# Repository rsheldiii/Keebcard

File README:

#Keebcard code

This project is a little rough right now, I had a backup failure that wiped out some of the code. I'll be fixing this up in the coming weeks and getting everything working again.

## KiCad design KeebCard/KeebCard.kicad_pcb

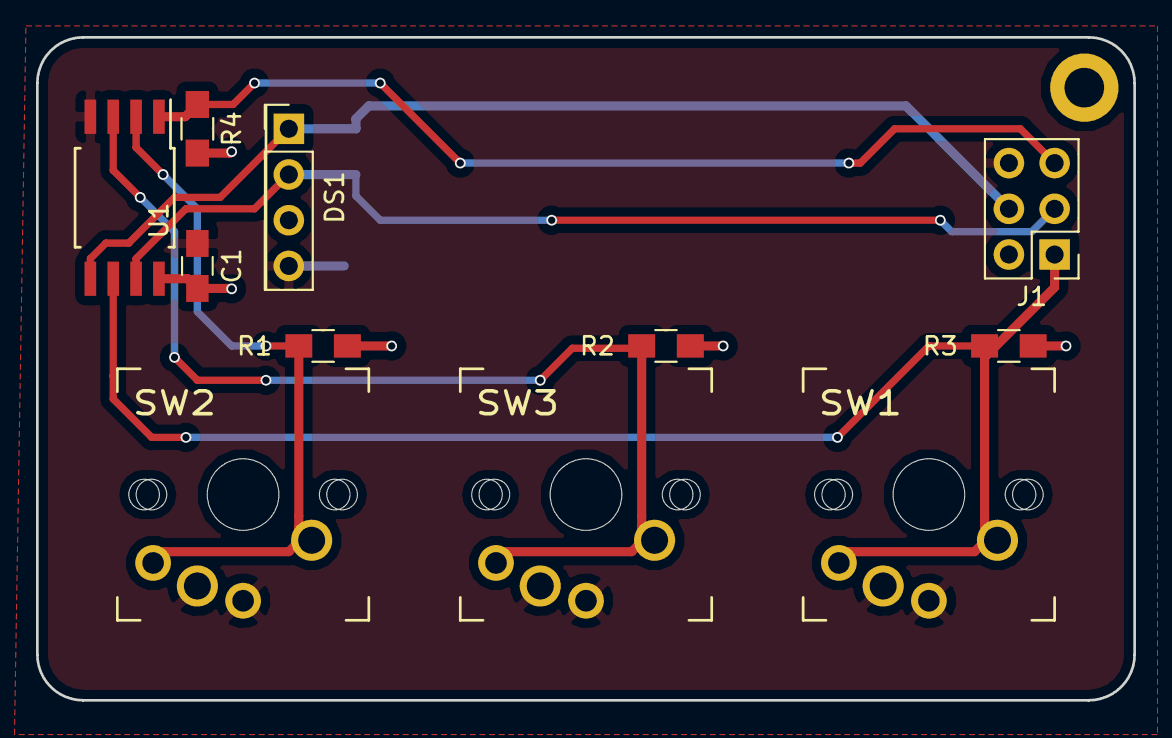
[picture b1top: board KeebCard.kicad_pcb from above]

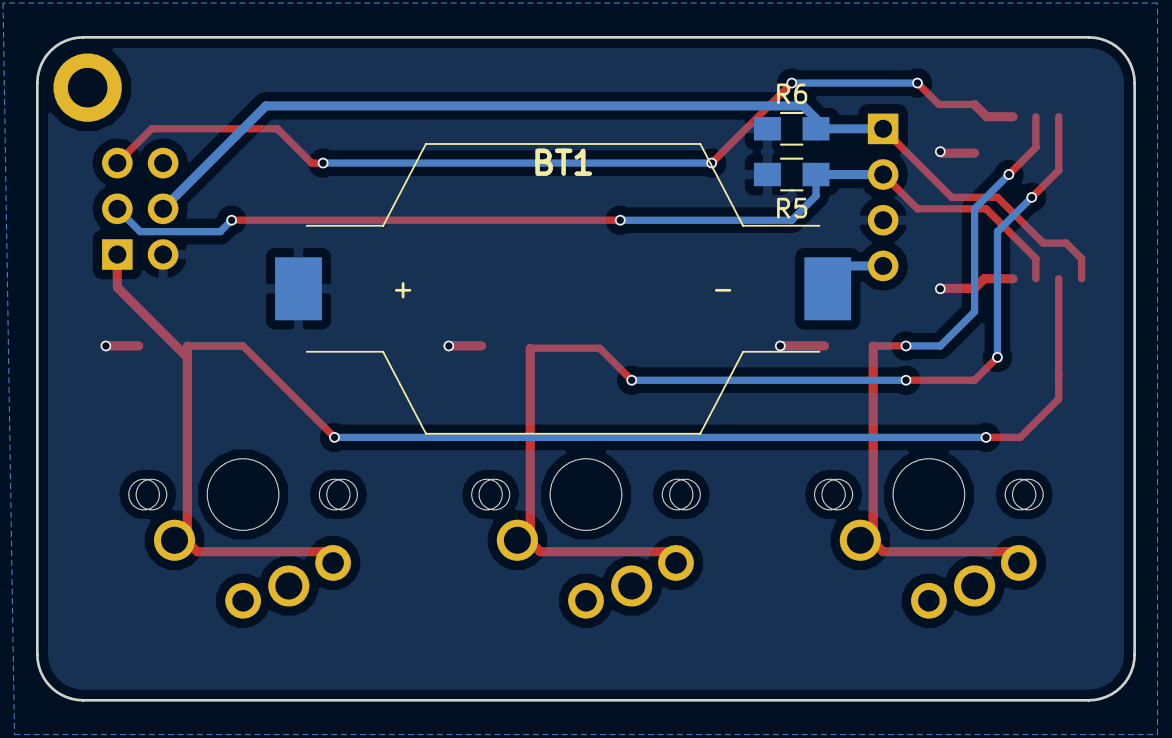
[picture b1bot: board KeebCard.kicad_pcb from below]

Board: 2 copper layers, 61.0 x 36.8 mm, 14 parts (3 on the bottom side), 8 nets.

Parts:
BT1: CR2032; SMTU2032
C1: 100nF; C_0805_HandSoldering
DS1: SSD1306-128x32; SSD1306_OLED_Display_128x32
J1: Conn_02x03_Odd_Even; Pin_Header_Straight_2x03_Pitch2.54mm
R1, R2, R3, R4: 22K; R_0805_HandSoldering
R5, R6: 4.7k; R_0805_HandSoldering
SW1, SW2, SW3: SW_Push; CHERRY_CHOC_PCB
U1: ATTINY85-20SU

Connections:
/PB0: DS1.4, J1.4, R6.1, U1.5
/PB1: J1.1, R3.2, SW1.2, U1.6
/PB2: DS1.3, J1.3, R5.1, U1.7
/PB3: R1.2, SW2.2, U1.2
/PB4: R2.2, SW3.2, U1.3
/PB5: J1.5, R4.1, U1.1
GND: BT1.2, C1.2, DS1.1, J1.6, SW1.1, SW2.1, SW3.1, U1.4
VCC: BT1.1, C1.1, DS1.2, J1.2, R1.1, R2.1, R3.1, R4.2, R5.2, R6.2, U1.8

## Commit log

2019-08-02 Add current code as-is
2019-08-02 Rename README to README.md
2019-08-03 Rename so arduino doesn't complain
2019-08-03 Make compiler happy again
    previously upgraded to a newer version of tiny4koled that doesn't like tiny4koled.h to be included, else there are multiple declaration problems. switched to a pointer and tiny4koled_common.h and it 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
2019-08-09 work on snake a whole bunch
2019-08-10 do even more work on Snake
    I have better commit messages in my professional life I swear
2019-08-19 Update gitignore for Kicad files
2019-08-19 Get Tetris functioning
    not perfect yet
2019-08-19 Add Kicad project
2019-08-19 Add Gerbers
2019-10-02 Last minute PCB changes
2019-10-02 Pong, final version, first pass
2019-10-02 _oled
2019-10-02 revert weird changes
    some weird state accidentally got committed. Should really switch to linux with this
2019-10-02 Reorganize and update comments
2019-10-02 Fix bouncing
2019-10-03 no higher than 999
2019-10-03 Sundries
2019-10-08 clear() tweaks
    It's not meant to work in addressing mode 1
2019-10-08 break out SnakePath and use quad directions
    Finally incorporating the 4x memory savings we get via bit packing. 200 is not a hard limit yet, I need to evaluate some more local vairables and figure out why my overhead is so high. 256 should the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
2019-10-08 Fix setNewFoodPosition
    we were randomly picking points and checking if they collide which was not gonna scale at all. We still try to do that, but now if we fail we scan for segments with open pixels, randomly pick one, an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
2019-10-11 whoops, that was necessary
2019-10-11 last tweaks I swear
    reinstitute easier english shots, correct early AI return, add minimal randomness to serve. swap buttons
2019-10-19 Snake updates
    trying to allow for rerunning the program, accounting for memory limits with a smaller board
2019-10-23 add provisional assembly video
    I want to reshoot it, I ramble a lot
2019-10-26 add flashing tutorial
2019-10-28 Edge case cleanup
    Pretty sure this is going to be the production version unless I find anything wrong about it tomorrow. fix a lot of bounding edge cases and revamp fallback food placement logic because it was dead wr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
2019-10-28 Update KeebCard.jpg
    slightly better picture
2019-11-03 Added media links
2019-12-02 Fix corruption on game over (I think)
    every once in a while Snake corrupts when the snake collides with the upper wall. I think the y coordinate is wrapping past zero and accessing memory it shouldn't, and I think this fixes it
2019-12-02 Tetris updates
    found my old code, implemented auto-down, removed "ticks per frame" concept from event loop, added rotation "kicking" where the piece will move 1 spot to the left or right if it allows a rotation tha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
2019-12-03 bash my way through a pin interrupt input system. fix some bugs on the way
2019-12-06 implement much better tetronimo selection logic
2019-12-07 fix scoring, speed, and level logic
2019-12-08 fix pieces
2019-12-08 sundries. speed things up a bit. debounce buttons. always rotate
2019-12-09 fix tetris score
2020-01-22 fix bad kicad lib declarations
2020-01-22 fix up footprint libraries too
2020-02-13 Add Conway
2020-02-19 Update README.md
    troubleshooting info
2020-02-19 Disable Entropy for now
2020-04-12 Fix Conway
    RIP. Switches board to big-endian and fixes a few issues - like incorrectly using UPosition for negative deltas in the neighbor function and < vs <= mishap
2020-05-19 Add cases
2020-05-26 Add case video link
2020-05-26 Spring cleaning in README.md
2020-05-31 two changes, one i have commented out a switchframe in tetris that was causing the score to not show, two I have added a simple business card
2020-05-31 fixed a bug in buisnesscard and changed text to KeebCard
2023-07-15 Update README.md for OpenSauce
2024-01-06 finally forever-more fix Tetris buttons
2025-07-28 restart logic
2025-08-07 some QoL changes
2025-09-01 seed srand from eeprom
